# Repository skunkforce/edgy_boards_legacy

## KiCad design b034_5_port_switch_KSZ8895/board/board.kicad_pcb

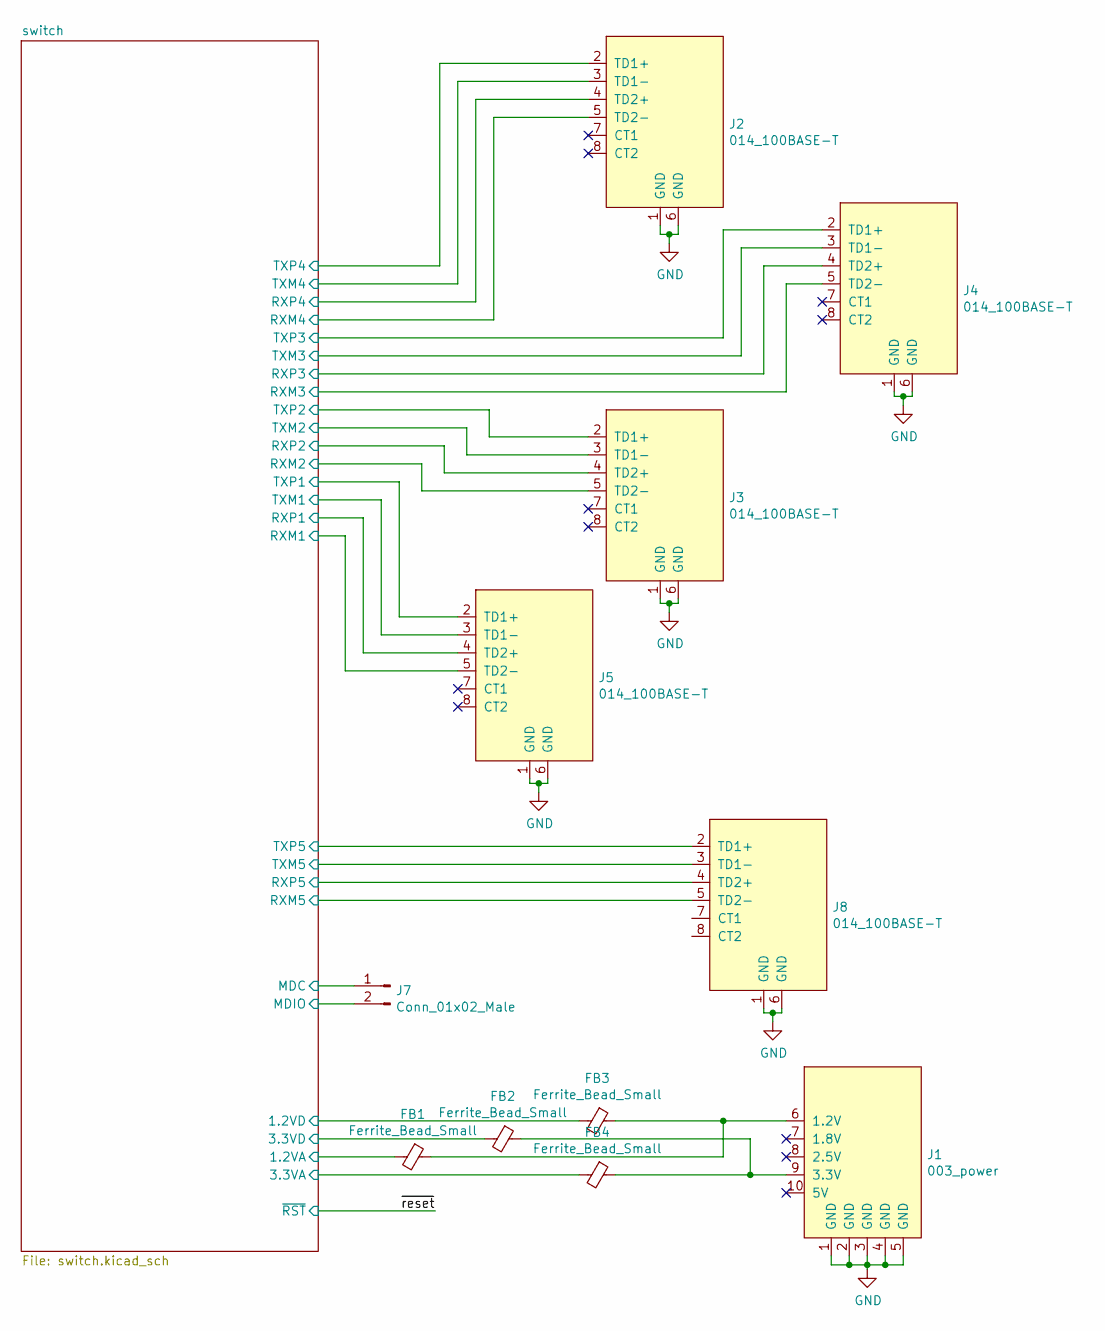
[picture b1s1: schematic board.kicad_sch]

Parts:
FB1, FB2, FB3, FB4: Ferrite_Bead_Small; L_0805_2012Metric
J1: 003_power; on_edge_2x05_device
J2, J3, J4, J5, J8: 014_100BASE-T; on_edge_2x05_host
J7: Conn_01x02_Male; PinHeader_1x02_P2.54mm_Vertical

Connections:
/switch/1.2VA: FB1.2; also elsewhere on the board
/switch/1.2VD: FB3.2; also elsewhere on the board
/switch/3.3VA: FB4.2; also elsewhere on the board
/switch/3.3VD: FB2.2; also elsewhere on the board
/switch/MDC: J7.1; also elsewhere on the board
/switch/MDIO: J7.2; also elsewhere on the board
/switch/RXM1: J5.5 (TD2-); also elsewhere on the board
/switch/RXM2: J3.5 (TD2-); also elsewhere on the board
/switch/RXM3: J4.5 (TD2-); also elsewhere on the board
/switch/RXM4: J2.5 (TD2-); also elsewhere on the board
/switch/RXM5: J8.5 (TD2-); also elsewhere on the board
/switch/RXP1: J5.4 (TD2+); also elsewhere on the board
/switch/RXP2: J3.4 (TD2+); also elsewhere on the board
/switch/RXP3: J4.4 (TD2+); also elsewhere on the board
/switch/RXP4: J2.4 (TD2+); also elsewhere on the board
/switch/RXP5: J8.4 (TD2+); also elsewhere on the board
/switch/TXM1: J5.3 (TD1-); also elsewhere on the board
/switch/TXM2: J3.3 (TD1-); also elsewhere on the board
/switch/TXM3: J4.3 (TD1-); also elsewhere on the board
/switch/TXM4: J2.3 (TD1-); also elsewhere on the board
/switch/TXM5: J8.3 (TD1-); also elsewhere on the board
/switch/TXP1: J5.2 (TD1+); also elsewhere on the board
/switch/TXP2: J3.2 (TD1+); also elsewhere on the board
/switch/TXP3: J4.2 (TD1+); also elsewhere on the board
/switch/TXP4: J2.2 (TD1+); also elsewhere on the board
/switch/TXP5: J8.2 (TD1+); also elsewhere on the board
GND: J1.1 (GND), J1.2 (GND), J1.3 (GND), J1.4 (GND), J1.5 (GND), J2.1 (GND), J2.6 (GND), J3.1 (GND), J3.6 (GND), J4.1 (GND), J4.6 (GND), J5.1 (GND), J5.6 (GND), J8.1 (GND), J8.6 (GND); also elsewhere on the board
unnamed: FB1.1, FB3.1, J1.6 (1.2V)
unnamed: FB2.1, FB4.1, J1.9 (3.3V)

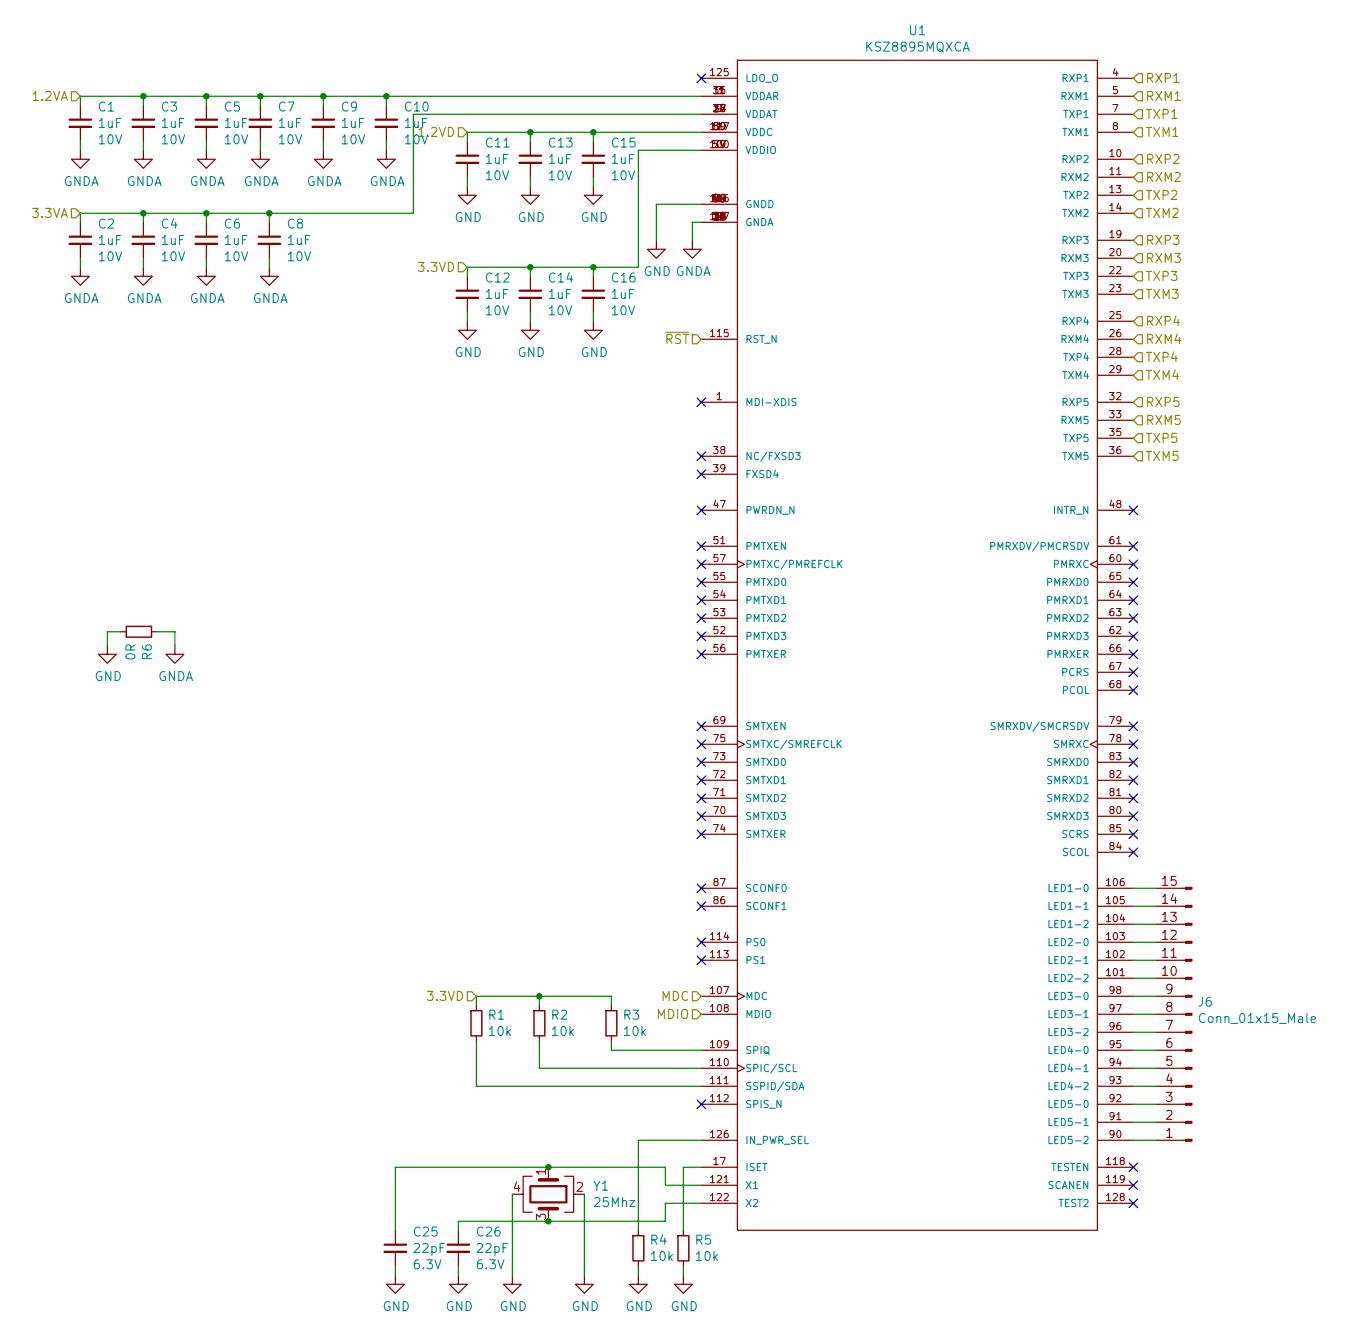
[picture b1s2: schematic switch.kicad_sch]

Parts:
C1, C2, C3, C4, C5, C6, C7, C8, C9, C10, C11, C12, C13, C14, C15, C16: 1uF; C_0402_1005Metric; Voltage 10V; MPN CL05A105MP5NNNC; Digi-Key_PN 1276-1448-1-ND
C25, C26: 22pF; C_0402_1005Metric; Voltage 6.3V; Digi-Key_PN 1276-1665-1-ND
J6: Conn_01x15_Male; PinHeader_2x08_P2.54mm_Vertical
R1, R2, R3, R4, R5: 10k; R_0402_1005Metric
R6: 0R; R_0805_2012Metric
U1: KSZ8895MQXCA; LQFP-128_14x20mm_P0.5mm; Digi-Key_PN 576-4855-ND
Y1: 25Mhz; Crystal_SMD_2520-4Pin_2.5x2.0mm; MPN ECS-250-18-36B-CKY-TR

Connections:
/switch/1.2VA: C1.1, C3.1, C5.1, C7.1, C9.1, C10.1, U1.3 (VDDAR), U1.15 (VDDAR), U1.31 (VDDAR); also elsewhere on the board
/switch/1.2VD: C11.1, C13.1, C15.1, U1.50 (VDDC), U1.89 (VDDC), U1.117 (VDDC); also elsewhere on the board
/switch/3.3VA: C2.1, C4.1, C6.1, C8.1, U1.9 (VDDAT), U1.18 (VDDAT), U1.24 (VDDAT), U1.37 (VDDAT); also elsewhere on the board
/switch/3.3VD: C12.1, C14.1, C16.1, R1.1, R2.1, R3.1, U1.59 (VDDIO), U1.77 (VDDIO), U1.100 (VDDIO); also elsewhere on the board
/switch/MDC: U1.107 (MDC); also elsewhere on the board
/switch/MDIO: U1.108 (MDIO); also elsewhere on the board
/switch/RXM1: U1.5 (RXM1); also elsewhere on the board
/switch/RXM2: U1.11 (RXM2); also elsewhere on the board
/switch/RXM3: U1.20 (RXM3); also elsewhere on the board
/switch/RXM4: U1.26 (RXM4); also elsewhere on the board
/switch/RXM5: U1.33 (RXM5); also elsewhere on the board
/switch/RXP1: U1.4 (RXP1); also elsewhere on the board
/switch/RXP2: U1.10 (RXP2); also elsewhere on the board
/switch/RXP3: U1.19 (RXP3); also elsewhere on the board
/switch/RXP4: U1.25 (RXP4); also elsewhere on the board
/switch/RXP5: U1.32 (RXP5); also elsewhere on the board
/switch/TXM1: U1.8 (TXM1); also elsewhere on the board
/switch/TXM2: U1.14 (TXM2); also elsewhere on the board
/switch/TXM3: U1.23 (TXM3); also elsewhere on the board
/switch/TXM4: U1.29 (TXM4); also elsewhere on the board
/switch/TXM5: U1.36 (TXM5); also elsewhere on the board
/switch/TXP1: U1.7 (TXP1); also elsewhere on the board
/switch/TXP2: U1.13 (TXP2); also elsewhere on the board
/switch/TXP3: U1.22 (TXP3); also elsewhere on the board
/switch/TXP4: U1.28 (TXP4); also elsewhere on the board
/switch/TXP5: U1.35 (TXP5); also elsewhere on the board
GND: C11.2, C12.2, C13.2, C14.2, C15.2, C16.2, C25.2, C26.2, R4.2, R5.2, R6.2, U1.49 (GNDD), U1.58 (GNDD), U1.76 (GNDD), U1.88 (GNDD), U1.99 (GNDD), U1.116 (GNDD), Y1.2, Y1.4; also elsewhere on the board
GNDA: C1.2, C2.2, C3.2, C4.2, C5.2, C6.2, C7.2, C8.2, C9.2, C10.2, R6.1, U1.2 (GNDA), U1.6 (GNDA), U1.12 (GNDA), U1.16 (GNDA), U1.21 (GNDA), U1.27 (GNDA), U1.30 (GNDA), U1.34 (GNDA), U1.127 (GNDA)
unnamed: C25.1, U1.121 (X1), Y1.1
unnamed: C26.1, U1.122 (X2), Y1.3
unnamed: J6.1, U1.90 (LED5-2)
unnamed: J6.2, U1.91 (LED5-1)
unnamed: J6.3, U1.92 (LED5-0)
unnamed: J6.4, U1.93 (LED4-2)
unnamed: J6.5, U1.94 (LED4-1)
unnamed: J6.6, U1.95 (LED4-0)
unnamed: J6.7, U1.96 (LED3-2)
unnamed: J6.8, U1.97 (LED3-1)
unnamed: J6.9, U1.98 (LED3-0)
unnamed: J6.10, U1.101 (LED2-2)
unnamed: J6.11, U1.102 (LED2-1)
unnamed: J6.12, U1.103 (LED2-0)
unnamed: J6.13, U1.104 (LED1-2)
unnamed: J6.14, U1.105 (LED1-1)
unnamed: J6.15, U1.106 (LED1-0)
unnamed: R1.2, U1.111 (SSPID/SDA)
unnamed: R2.2, U1.110 (SPIC/SCL)
unnamed: R3.2, U1.109 (SPIQ)
unnamed: R4.1, U1.126 (IN_PWR_SEL)
unnamed: R5.1, U1.17 (ISET)

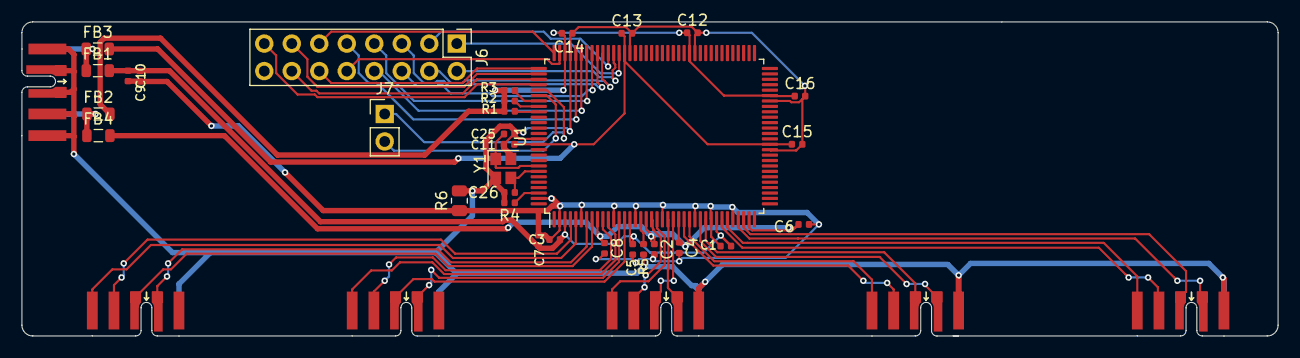
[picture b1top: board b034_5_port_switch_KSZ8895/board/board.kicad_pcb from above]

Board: 2 copper layers, 116.0 x 29.0 mm, 38 parts (0 on the bottom side), 52 nets.

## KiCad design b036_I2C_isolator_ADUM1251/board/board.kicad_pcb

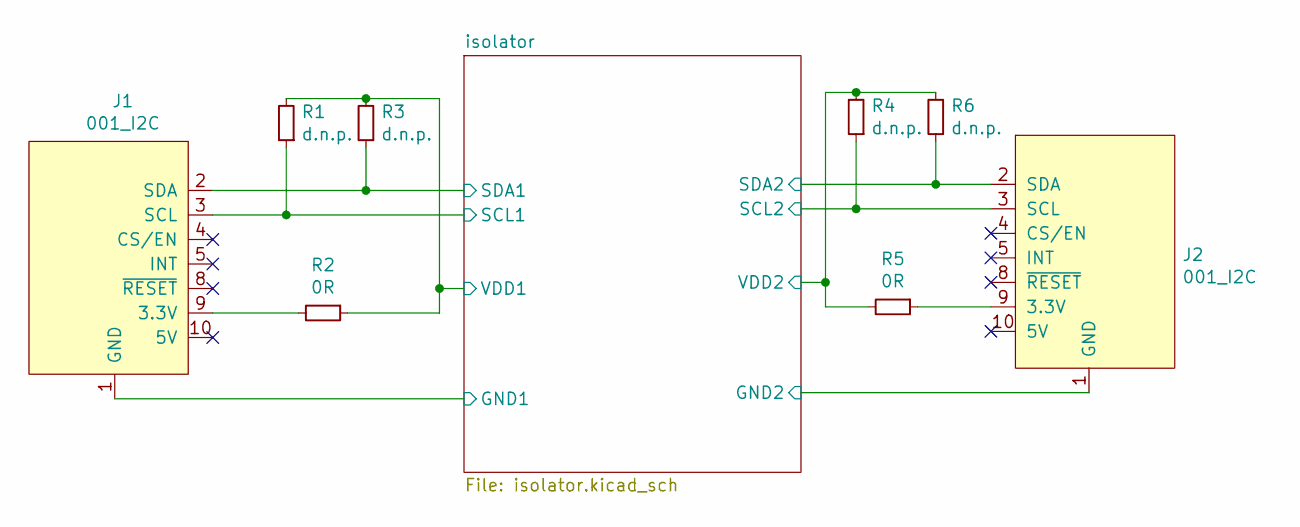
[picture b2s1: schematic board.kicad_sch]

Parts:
J1: 001_I2C; on_edge_2x05_device
J2: 001_I2C; on_edge_2x05_host
R1, R3, R4, R6: d.n.p.; R_0603_1608Metric
R2, R5: 0R; R_0603_1608Metric

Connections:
/isolator/GND1: J1.1 (GND); also elsewhere on the board
/isolator/GND2: J2.1 (GND); also elsewhere on the board
/isolator/SCL1: J1.3 (SCL), R1.1; also elsewhere on the board
/isolator/SCL2: J2.3 (SCL), R4.1; also elsewhere on the board
/isolator/SDA1: J1.2 (SDA), R3.1; also elsewhere on the board
/isolator/SDA2: J2.2 (SDA), R6.1; also elsewhere on the board
/isolator/VDD1: R1.2, R2.1, R3.2; also elsewhere on the board
/isolator/VDD2: R4.2, R5.2, R6.2; also elsewhere on the board
unnamed: J1.9 (3.3V), R2.2
unnamed: J2.9 (3.3V), R5.1

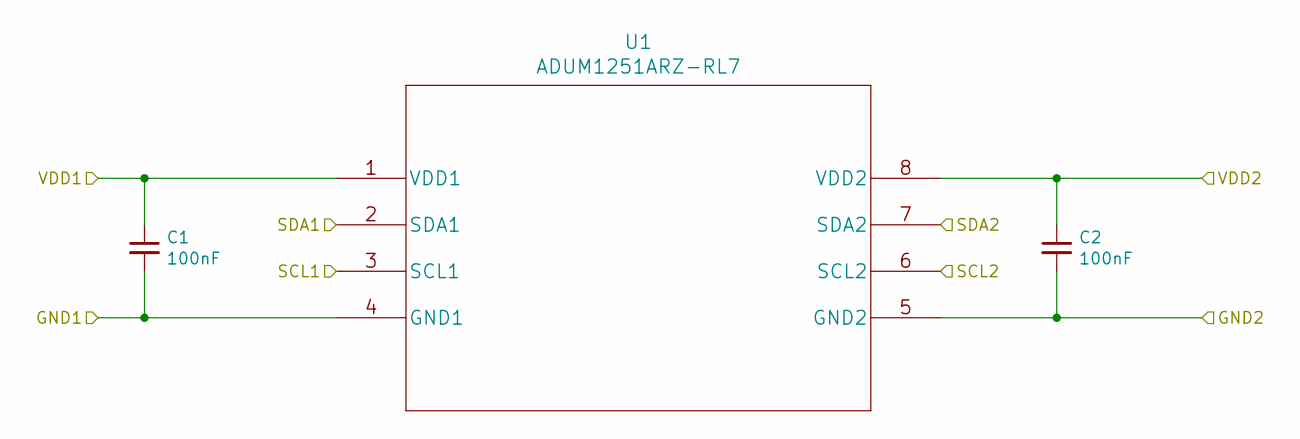
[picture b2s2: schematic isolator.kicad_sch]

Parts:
C1, C2: 100nF; C_0603_1608Metric
U1: ADUM1251ARZ-RL7; SOIC-8_3.9x4.9mm_P1.27mm; MPN ADUM1251ARZ-RL7; Digi-Key_PN ADUM1251ARZ-RL7CT-ND

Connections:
/isolator/GND1: C1.2, U1.4 (GND1); also elsewhere on the board
/isolator/GND2: C2.2, U1.5 (GND2); also elsewhere on the board
/isolator/SCL1: U1.3 (SCL1); also elsewhere on the board
/isolator/SCL2: U1.6 (SCL2); also elsewhere on the board
/isolator/SDA1: U1.2 (SDA1); also elsewhere on the board
/isolator/SDA2: U1.7 (SDA2); also elsewhere on the board
/isolator/VDD1: C1.1, U1.1 (VDD1); also elsewhere on the board
/isolator/VDD2: C2.1, U1.8 (VDD2); also elsewhere on the board

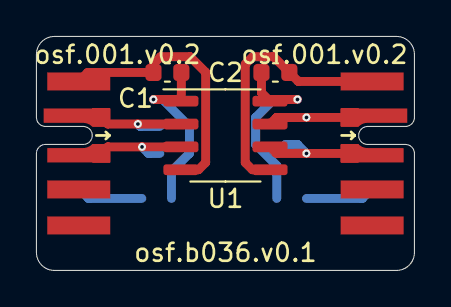
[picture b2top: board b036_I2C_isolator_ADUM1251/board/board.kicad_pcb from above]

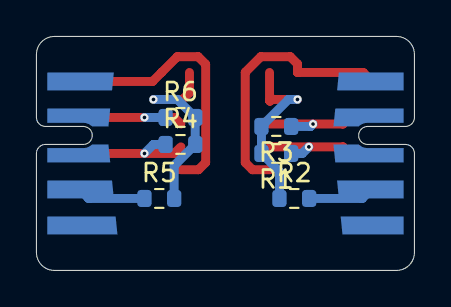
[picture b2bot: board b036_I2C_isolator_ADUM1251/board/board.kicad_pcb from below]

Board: 2 copper layers, 21.0 x 13.0 mm, 11 parts (6 on the bottom side), 10 nets.

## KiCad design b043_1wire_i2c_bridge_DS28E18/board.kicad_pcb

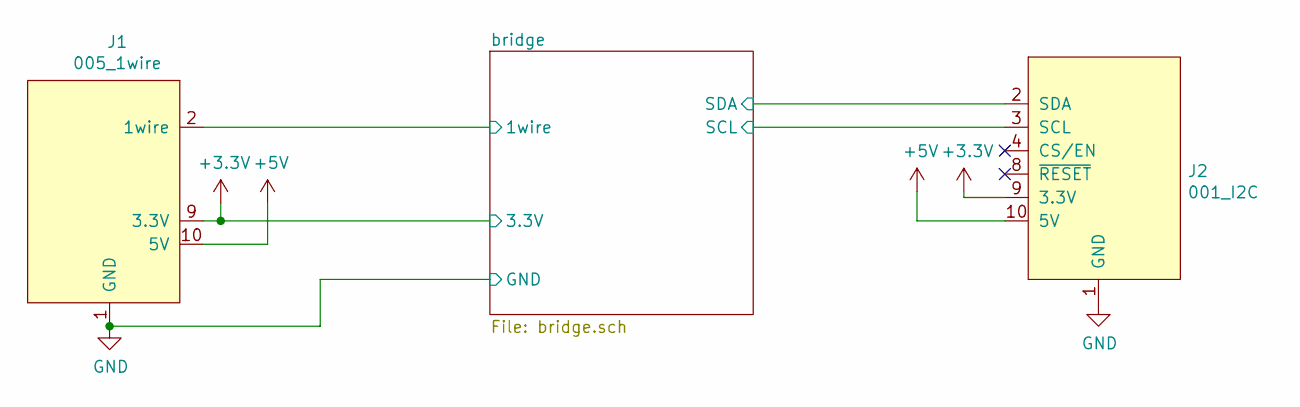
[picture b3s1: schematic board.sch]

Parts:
J1: 005_1wire; on_edge_2x05_device
J2: 001_I2C; on_edge_2x05_host

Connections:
+3V3: J1.9 (3.3V), J2.9 (3.3V); also elsewhere on the board
+5V: J1.10 (5V), J2.10 (5V)
/bridge/1wire: J1.2 (1wire); also elsewhere on the board
/bridge/SCL: J2.3 (SCL); also elsewhere on the board
/bridge/SDA: J2.2 (SDA); also elsewhere on the board
GND: J1.1 (GND), J2.1 (GND); also elsewhere on the board

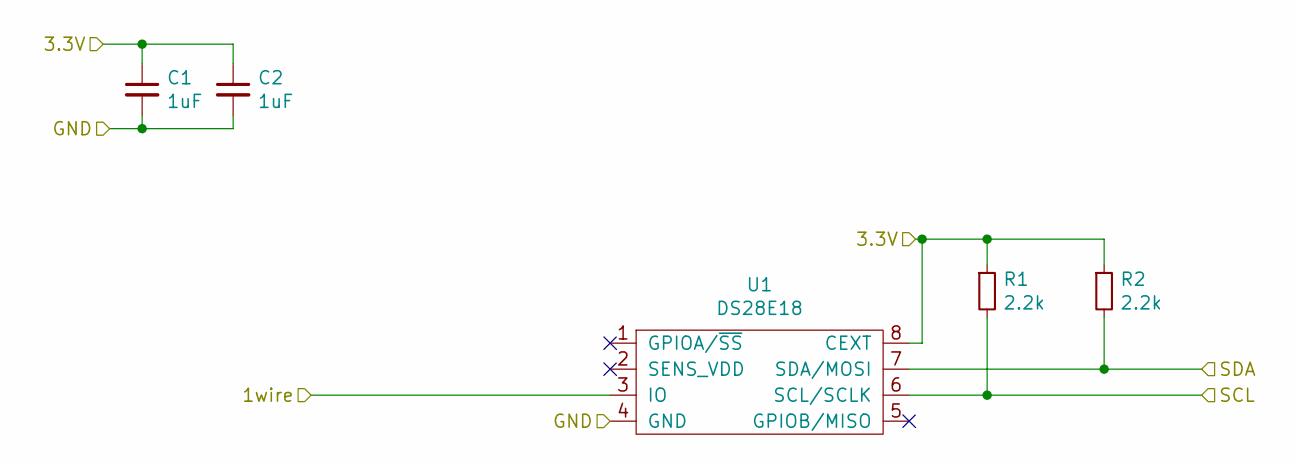
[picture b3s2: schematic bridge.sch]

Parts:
C1, C2: 1uF; C_0603_1608Metric
R1, R2: 2.2k; R_0603_1608Metric
U1: DS28E18; TDFN-8-1EP_3x2mm_P0.5mm_EP1.80x1.65mm

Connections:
+3V3: C1.1, C2.1, R1.1, R2.1, U1.8 (CEXT); also elsewhere on the board
/bridge/1wire: U1.3 (IO); also elsewhere on the board
/bridge/SCL: R1.2, U1.6 (SCL/SCLK); also elsewhere on the board
/bridge/SDA: R2.2, U1.7 (SDA/MOSI); also elsewhere on the board
GND: C1.2, C2.2, U1.4 (GND), U1.9 (GND); also elsewhere on the board

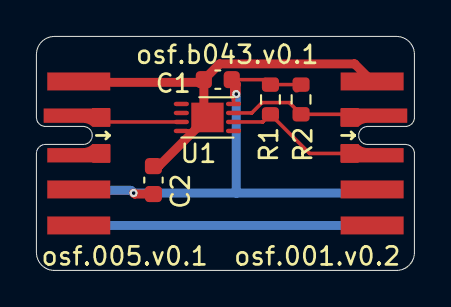
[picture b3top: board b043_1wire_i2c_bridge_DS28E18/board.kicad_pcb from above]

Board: 2 copper layers, 21.0 x 13.0 mm, 7 parts (0 on the bottom side), 6 nets.

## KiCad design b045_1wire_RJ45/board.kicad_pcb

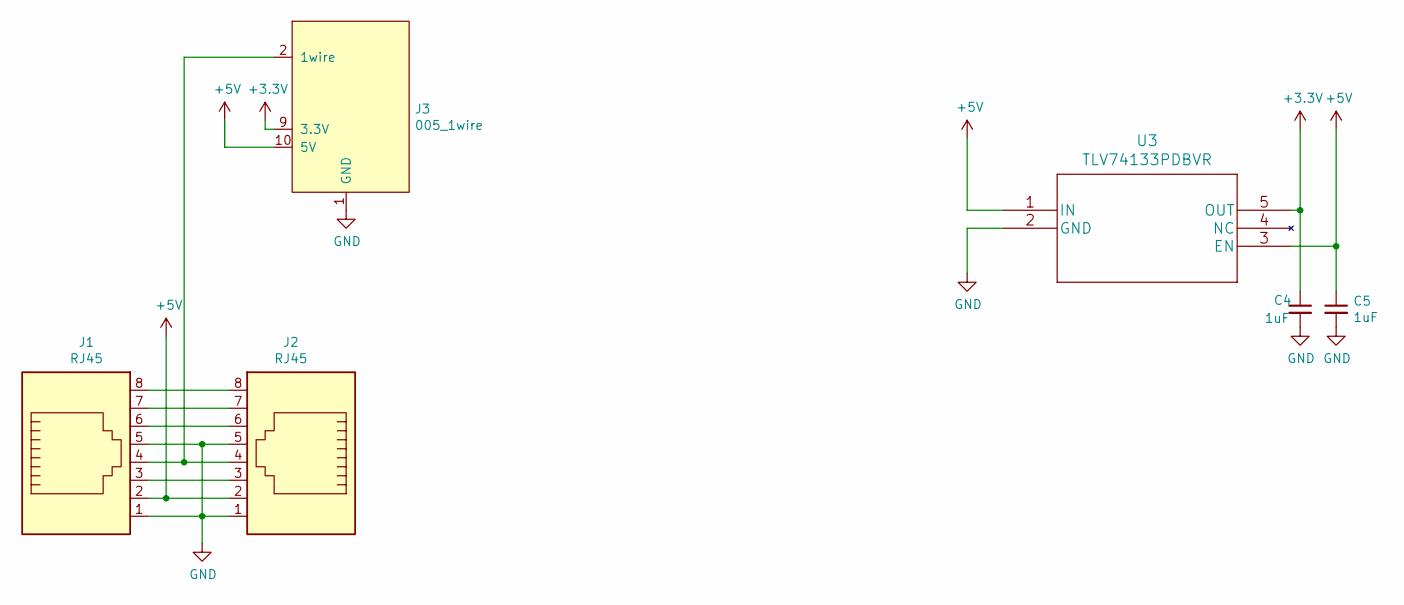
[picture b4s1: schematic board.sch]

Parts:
C4, C5: 1uF; C_0603_1608Metric
J1, J2: RJ45; RJ45_Amphenol_54602-x08_Horizontal; MPN 54602-x08; Digi-Key_PN 609-1046-ND
J3: 005_1wire; on_edge_2x05_host
U3: TLV74133PDBVR; SOT-23-5; MPN TLV74133PDBVR; Digi-Key_PN 296-48987-2-ND

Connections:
+3V3: C4.1, J3.9 (3.3V), U3.5 (OUT)
+5V: C5.1, J1.2, J2.2, J3.10 (5V), U3.1 (IN), U3.3 (EN)
GND: C4.2, C5.2, J1.1, J1.5, J2.1, J2.5, J3.1 (GND), U3.2 (GND)
unnamed: J1.3, J2.3
unnamed: J1.4, J2.4, J3.2 (1wire)
unnamed: J1.6, J2.6
unnamed: J1.7, J2.7
unnamed: J1.8, J2.8

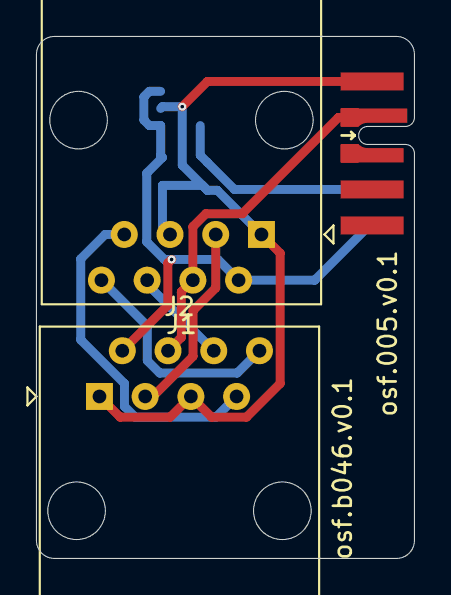
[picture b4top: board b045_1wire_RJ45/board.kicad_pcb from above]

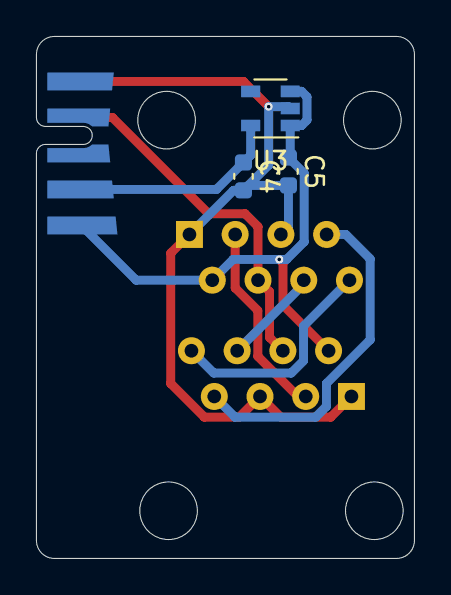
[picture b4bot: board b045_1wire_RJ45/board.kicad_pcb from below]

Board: 2 copper layers, 21.0 x 29.0 mm, 6 parts (3 on the bottom side), 8 nets.

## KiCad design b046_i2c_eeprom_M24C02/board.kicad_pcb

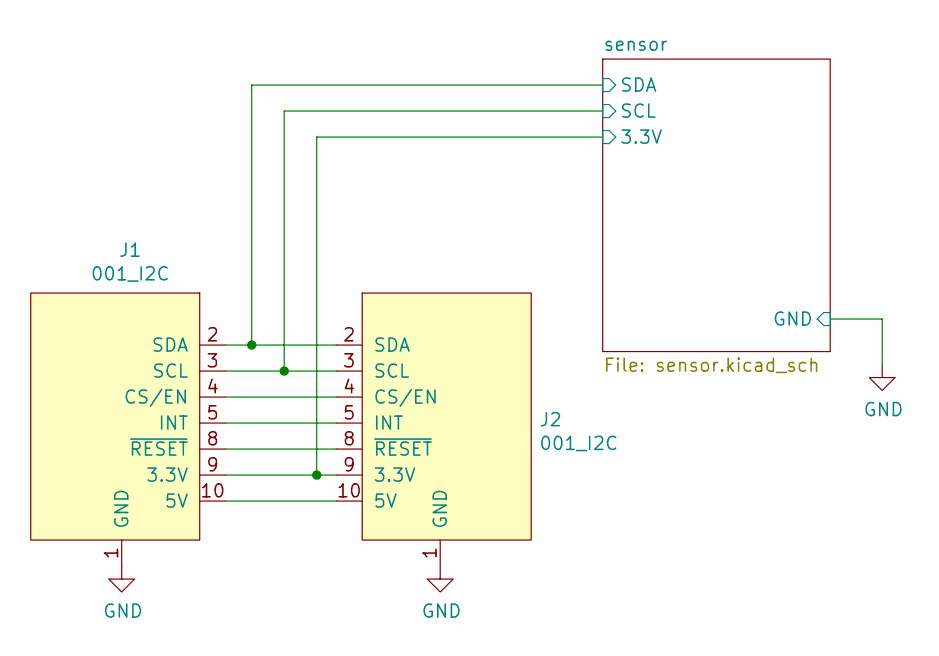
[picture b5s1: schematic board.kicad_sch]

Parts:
J1: 001_I2C; on_edge_2x05_device
J2: 001_I2C; on_edge_2x05_host

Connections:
/sensor/3.3V: J1.9 (3.3V), J2.9 (3.3V); also elsewhere on the board
/sensor/SCL: J1.3 (SCL), J2.3 (SCL); also elsewhere on the board
/sensor/SDA: J1.2 (SDA), J2.2 (SDA); also elsewhere on the board
GND: J1.1 (GND), J2.1 (GND); also elsewhere on the board
unnamed: J1.4 (CS/EN), J2.4 (CS/EN)
unnamed: J1.5 (INT), J2.5 (INT)
unnamed: J1.8 (~RESET), J2.8 (~RESET)
unnamed: J1.10 (5V), J2.10 (5V)

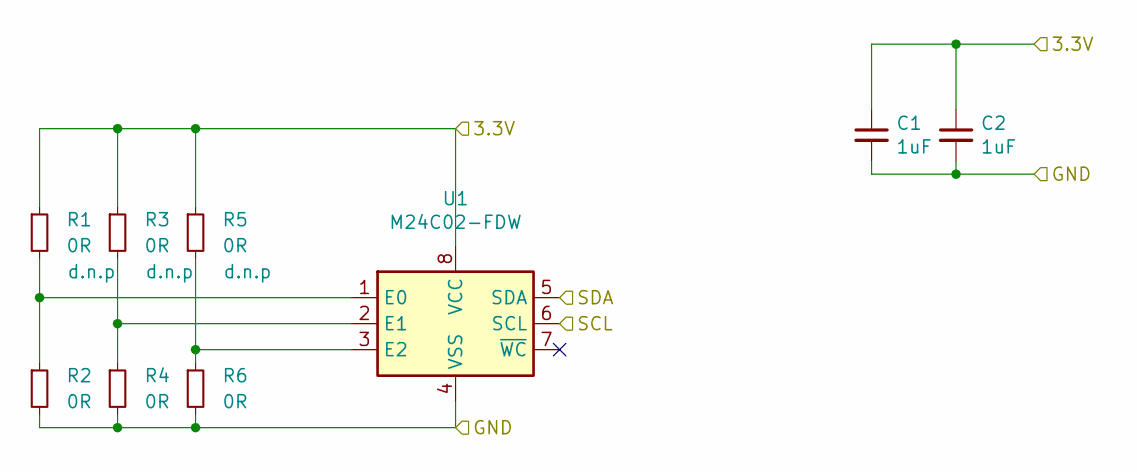
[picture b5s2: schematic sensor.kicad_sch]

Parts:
C1, C2: 1uF; C_0603_1608Metric
R1, R2, R3, R4, R5, R6: 0R; R_0603_1608Metric
U1: M24C02-FDW; TSSOP-8_4.4x3mm_P0.65mm

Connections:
/sensor/3.3V: C1.1, C2.1, R1.1, R3.1, R5.1, U1.8 (VCC); also elsewhere on the board
/sensor/SCL: U1.6 (SCL); also elsewhere on the board
/sensor/SDA: U1.5 (SDA); also elsewhere on the board
GND: C1.2, C2.2, R2.2, R4.2, R6.2, U1.4 (VSS); also elsewhere on the board
unnamed: R1.2, R2.1, U1.1 (E0)
unnamed: R3.2, R4.1, U1.2 (E1)
unnamed: R5.2, R6.1, U1.3 (E2)

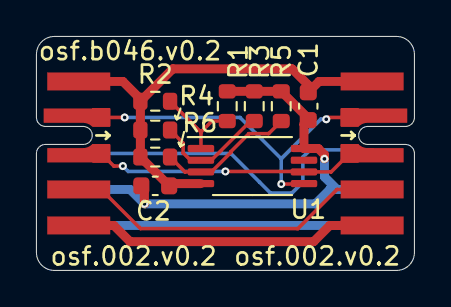
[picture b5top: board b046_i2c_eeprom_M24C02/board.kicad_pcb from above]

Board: 2 copper layers, 21.0 x 13.0 mm, 11 parts (0 on the bottom side), 11 nets.

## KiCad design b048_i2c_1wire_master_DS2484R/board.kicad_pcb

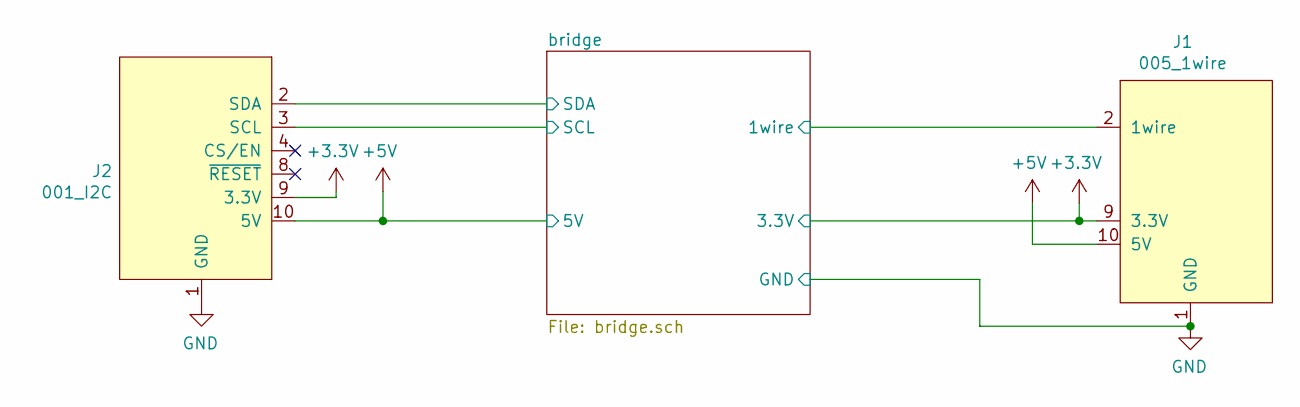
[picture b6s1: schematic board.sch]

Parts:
J1: 005_1wire; on_edge_2x05_host
J2: 001_I2C; on_edge_2x05_device

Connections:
+3V3: J1.9 (3.3V), J2.9 (3.3V); also elsewhere on the board
+5V: J1.10 (5V), J2.10 (5V); also elsewhere on the board
/bridge/1wire: J1.2 (1wire); also elsewhere on the board
/bridge/SCL: J2.3 (SCL); also elsewhere on the board
/bridge/SDA: J2.2 (SDA); also elsewhere on the board
GND: J1.1 (GND), J2.1 (GND); also elsewhere on the board

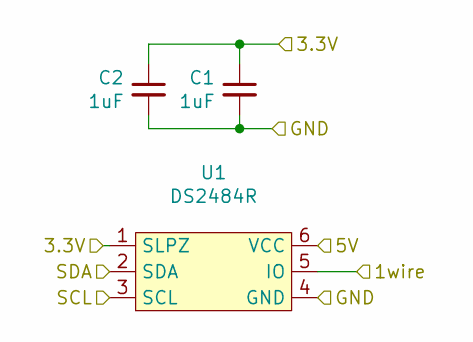
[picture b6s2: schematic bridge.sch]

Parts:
C1, C2: 1uF; C_0603_1608Metric
U1: DS2484R; TSOT-23-6

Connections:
+3V3: C1.1, C2.1, U1.1 (SLPZ); also elsewhere on the board
+5V: U1.6 (VCC); also elsewhere on the board
/bridge/1wire: U1.5 (IO); also elsewhere on the board
/bridge/SCL: U1.3 (SCL); also elsewhere on the board
/bridge/SDA: U1.2 (SDA); also elsewhere on the board
GND: C1.2, C2.2, U1.4 (GND); also elsewhere on the board

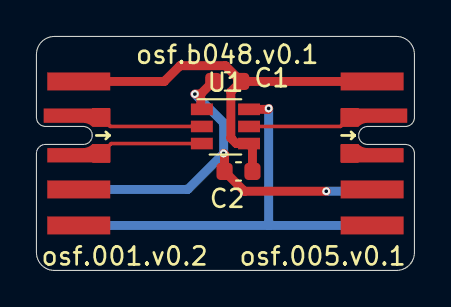
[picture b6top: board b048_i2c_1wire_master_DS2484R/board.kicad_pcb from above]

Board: 2 copper layers, 21.0 x 13.0 mm, 5 parts (0 on the bottom side), 6 nets.
